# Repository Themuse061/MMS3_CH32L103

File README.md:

Schematic should be good, but I haven't done routing yet

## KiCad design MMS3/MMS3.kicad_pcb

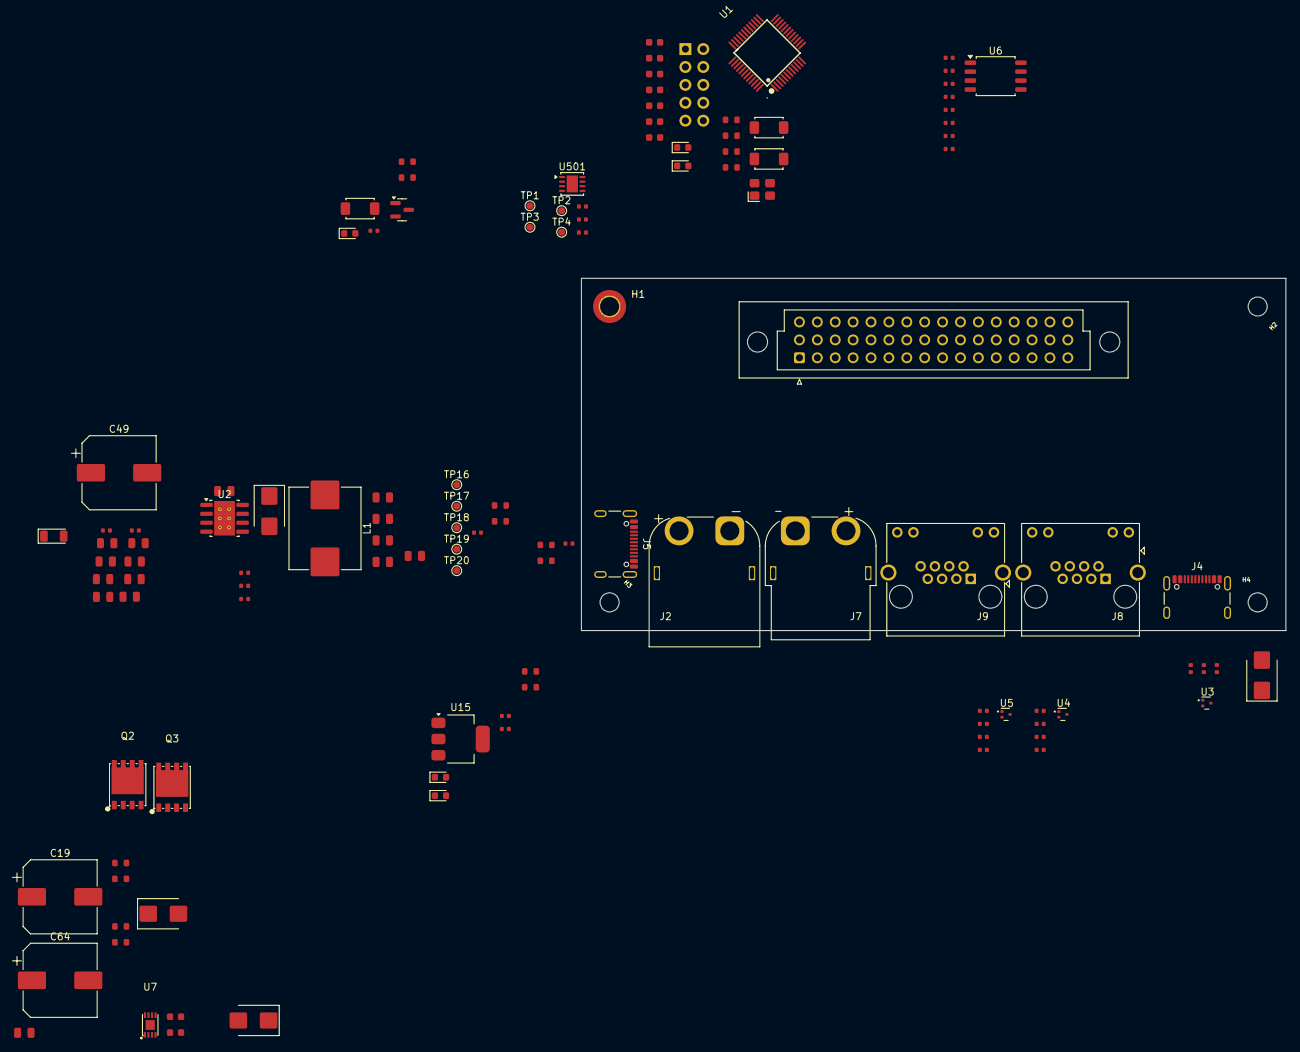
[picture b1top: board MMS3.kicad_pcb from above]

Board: 4 copper layers, 100.0 x 50.0 mm, 123 parts (1 on the bottom side), 77 nets, no tracks yet.

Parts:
C1, C2, C14: 10nF; C_0402
C3, C5: 12pF; C_0603
C4, C6, C15, C20, C27, C69, C74: 100nF; C_0402
C9, C10, C11, C12, C13, C16: 100nF; C_0603
C17: 1uF; C_0603
C18, C46, C47, C48, C50, C51: 22uF; C_0805
C19, C49, C64: 100uF; CP_Elec_10x10
C35, C36, C37, C38, C39, C40: 10uF; C_0805
C41, C42: 220nF; C_0805
C43: 47pF; C_0402
C44: 4.7nF; C_0402
C45: 100nF; C_0805
D1, D4, D6, D8, D9: Red; D_0603
D2: SMF58CA; D_SOD-123FL
D3, D5, D7, D10: SS510B; D_SMB
H1: M2.5 Mount; MountingHole_2.7mm_M2.5_DIN965_Pad_TopOnly
H2, H3, H4: M2.5 mount; MountingHole_2.7mm_M2.5
J1: 86093488324755V1LF; DIN41612_C2_3x16_Female_Vertical_THT
J2: AMASS XT60; AMASS_XT60PW-M_1x02_P7.20mm_Horizontal
J3: WCH Link; PinSocket_2x05_P2.54mm_Vertical
J4: USB_C_Receptacle_USB2.0_16P; USB_C_Receptacle_GCT_USB4105-xx-A_16P_TopMnt_Horizontal
J5: USB_PD; USB_C_Receptacle_GCT_USB4105-xx-A_16P_TopMnt_Horizontal
J7: AMASS XT60; AMASS_XT60PW-F_1x02_P7.20mm_Horizontal
J8, J9: RJ45_LED_Shielded; RJ45_Amphenol_RJHSE538X
L1: YSPI1050-100M; L_Sunlord_MWSA1005S
Q1: MMBT5401 200-300; Q_SOT-23
Q2, Q3: DOINGTER DON50N10-TL; PDFN-8_L5.8-W5.0-P1.27-LS6.1-BL
R1, R2, R3, R4: 220Ω; R_0402
R5, R6, R14: 33kΩ; R_0402
R7, R23, R24, R25, R26, R28, R29, R30, R501: 10kΩ; R_0402
R8: 1.5kΩ; R_0603
R9, R12, R13, R18: 1kΩ; R_0603
R10, R11: 10kΩ; R_0603
R15: 39kΩ; R_0603
R16: 12kΩ; R_0603
R17: 4.7kΩ; R_0603
R19: 47kΩ; R_0603
R20: 18kΩ; R_0603
R21, R22: 5.1kΩ; R_0603
R33, R34: 24.9kΩ; R_0402
R36: 43kΩ; R_0603
R37: 8.2kΩ; R_0402
R38: 12kΩ; R_0402
R39: 240kΩ; R_0603
S1, S2, S3: Tactile Button, 160gf; SW_TS-1088-AR02016
TP1, TP2, TP3, TP4, TP16, TP17, TP18, TP19, TP20: TestPoint; TestPoint_Pad_D1.0mm
U1: CH32L103C8T6_C22398291; LQFP-48_L7.0-W7.0-P0.50-LS9.0-BL
U2: TPS54560BDDA; Texas_R-PDSO-G8_EP2.95x4.9mm_Mask2.4x3.1mm_ThermalVias
U3, U4, U5: TPD2EUSB30DRTR-TP; SOT-723
U6: AT24C256C; SOIC-8_5.3x5.3mm_P1.27mm
U7: MX74502D23_C41433189; UDFN-8L_L2.0-W3.0-P0.50-BL-EP
U15: AMS1117-3.3; SOT-223-3_TabPin2
U501: TJA1044GTK_3Z; HVSON-8-1EP_3x3mm_P0.65mm_EP1.6x2.4mm
X1: X322525MOB4SI; OSC-SMD_4P-L3.2-W2.5-BL

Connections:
+3V3: C4.1, C9.1, C10.1, C11.1, C12.1, C13.1, C27.1, C69.1, D9.2, Q1.2 (E), R2.2, R3.2, R11.2, R28.1, R29.1, R30.1, S1.1 (A), S2.2 (B), U1.1 (VBAT), U1.9 (VDDA), U1.24 (VDD), U1.36 (VDD), U1.48 (VDD), U6.8 (VCC), U15.2 (VO), U501.5 (VIO)
+5V: C6.2, C19.1, C64.1, C74.1, D5.1, D7.1, D8.2, D10.1, J1.c2, J1.c3, J3.10, U15.3 (VI), U501.3 (VCC)
+12V stby: J1.c15, J8.6, J9.6
/CAN_TR2/CAN.+: J8.5, J9.5, U501.7 (CANH)
/CAN_TR2/CAN.-: J8.4, J9.4, U501.6 (CANL)
/CAN_TR2/CAN.RX: TP1.1 (1_1), TP4.1 (1_1), U1.45 (PB8), U501.4 (RXD)
/CAN_TR2/CAN.TX: TP2.1 (1_1), TP3.1 (1_1), U1.46 (PB9), U501.1 (TXD)
/CH32L103_Wrapper/CH32L103/BOOT0: R10.1, S2.1 (A), U1.44 (BOOT0)
/CH32L103_Wrapper/CH32L103/I2C1.SCL: J5.A5 (CC1), R22.1, U1.42 (PB6/CC1)
/CH32L103_Wrapper/CH32L103/I2C1.SDA: J5.B5 (CC2), R21.1, U1.43 (PB7/CC2)
/CH32L103_Wrapper/CH32L103/OSC_IN: C3.2, U1.5 (OSC_IN/PD0), X1.1 (OSC)
/CH32L103_Wrapper/CH32L103/OSC_Out: C5.2, U1.6 (OSC_OUT/PD1), X1.3 (OSC)
/CH32L103_Wrapper/CH32L103/PA13 (SWDIO): J3.4, U1.34 (PA13/SWDIO)
/CH32L103_Wrapper/CH32L103/PA14 (SWCLK): J3.2, U1.37 (PA14/SWCLK)
/CH32L103_Wrapper/CH32L103/UART1.RX: J3.3, R7.1, S1.2 (B), U1.31 (PA10)
/CH32L103_Wrapper/CH32L103/UART1.TX: D1.2, J3.1, U1.30 (PA9)
/CH32L103_Wrapper/CH32L103/~RST: J3.9, R11.1, S3.1 (A), U1.7 (NRST)
/CH32L103_Wrapper/Chainbus_addr0: J1.b3, U1.12 (PA2/ADC2/OPAO2)
/CH32L103_Wrapper/Chainbus_addr1: J1.b4, U1.13 (PA3/ADC3/OPAO0)
/CH32L103_Wrapper/Chainbus_addr2: J1.b5, U1.14 (PA4/ADC4/OPAO3)
/CH32L103_Wrapper/Chainbus_addr3: D4.1, J1.b1, U1.10 (PA0/WKUP/ADC0/OPAP4)
/CH32L103_Wrapper/Chainbus_addr4: J1.b2, U1.11 (PA1/ADC1/OPAN4)
/CH32L103_Wrapper/Chainbus_addr5: J1.b6, U1.15 (PA5/ADC5/OPAN3)
/CH32L103_Wrapper/Chainbus_addr6: J1.b7, U1.16 (PA6/ADC6/OPAP5/OPAN1)
/CH32L103_Wrapper/Chainbus_addr7: J1.b8, U1.17 (PA7/ADC7/OPAP3/OPAN5)
/CH32L103_Wrapper/I2C2.SCL: J1.b10, U1.22 (PB11/OPAN0), U6.6 (SCL)
/CH32L103_Wrapper/I2C2.SDA: J1.b9, U1.21 (PB10/OPAN2/OPAN6), U6.5 (SDA)
/CH32L103_Wrapper/PC13: D6.1, R8.1, U1.2 (PC13/TAMPER/RTC)
/CH32L103_Wrapper/SPI2.CS: J1.b11, U1.25 (PB12)
/CH32L103_Wrapper/SPI2.MISO: J1.b14, U1.28 (PB15/OPAP0)
/CH32L103_Wrapper/SPI2.MOSI: J1.b13, U1.27 (PB14/OPAP2)
/CH32L103_Wrapper/SPI2.SCK: J1.b12, U1.26 (PB13)
/CH32L103_Wrapper/UART4.RX: J1.b15, U1.19 (PB1/ADC9/OPAO1)
/CH32L103_Wrapper/UART4.TX: J1.b16, U1.18 (PB0/ADC8/OPAP1/OPAO4)
/CH32L103_Wrapper/USB1.D+: J4.A6 (D+), J4.B6 (D+), U1.33 (PA12/UDP), U3.1
/CH32L103_Wrapper/USB1.D-: J4.A7 (D-), J4.B7 (D-), U1.32 (PA11/UDM), U3.2
/I2C_Flash/A0: R23.1, R28.2, U6.1 (A0)
/I2C_Flash/A1: R24.1, R29.2, U6.2 (A1)
/I2C_Flash/A2: R25.1, R30.2, U6.3 (A2)
/MMS_CONNECTOR_DOWNSTREAM/CAN1.+: J8.2, J9.2
/MMS_CONNECTOR_DOWNSTREAM/CAN1.-: J8.1, J9.1
/MMS_CONNECTOR_DOWNSTREAM/USB_MMS_CONN.D+: J8.8, J9.8, U4.2, U5.2
/MMS_CONNECTOR_DOWNSTREAM/USB_MMS_CONN.D-: J8.7, J9.7, U4.1, U5.1
/PSU/Buck Converter/5V out: C46.1, C47.1, C48.1, C50.1, C51.1, D7.2, L1.2, R36.1, TP19.1 (1_1)
/PSU/Buck Converter/Cap_protec: C35.2, C36.1, C37.2, C38.1, C39.2, C40.1, C41.2, C42.1, R33.2, R34.1
/PSU/EN: R15.2, R16.1
/PSU/NMos1/D: C18.1, D10.2, Q3.5 (D), Q3.6 (D), Q3.7 (D), Q3.8 (D), Q3.9 (D)
/PSU/NMos/G: Q2.4 (G), Q3.4 (G), U7.2 (GATE)
/PSU/NMos/S: Q2.1 (S), Q2.2 (S), Q2.3 (S), Q3.1 (S), Q3.2 (S), Q3.3 (S), U7.3 (SRC)
/RXD2_LED: Q1.3 (C), R4.2
/TXD2_LED: R1.2, U1.20 (PB2/BOOT1)
/USB_Data/VBUS: C15.1, D5.2, J4.A4 (VBUS), J4.A9 (VBUS), J4.B4 (VBUS), J4.B9 (VBUS)
BRD_VIN: C16.1, C17.1, C20.1, C35.1, C37.1, C39.1, C41.1, C49.1, D2.1, J1.c5, J1.c6, J1.c7, J1.c8, J2.2, J5.A4 (VBUS), J5.A9 (VBUS), J5.B4 (VBUS), J5.B9 (VBUS), J7.2, Q2.5 (D), Q2.6 (D), Q2.7 (D), Q2.8 (D), Q2.9 (D), R15.1, R19.1, R33.1, TP16.1 (1_1), U2.2 (VIN), U2.3 (EN), U7.1 (VS), U7.5 (EN/UVLO)
GND: C1.2, C2.2, C3.1, C4.2, C5.1, C6.1, C9.2, C10.2, C11.2, C12.2, C13.2, C14.2, C15.2, C16.2, C18.2, C19.2, C20.2, C27.2, C36.2, C38.2, C40.2, C42.2, C43.2, C44.2, C46.2, C47.2, C48.2, C49.2, C50.2, C51.2, C64.2, C69.2, C74.2, D2.2, D3.2, H1.1 (1_1), J1.c1, J1.c4, J1.c9, J1.c10, J1.c11, J1.c12, J1.c16, J2.1, J3.6, J4.A1 (GND), J4.A12 (GND), J4.B1 (GND), J4.B12 (GND), J5.A1 (GND), J5.A12 (GND), J5.B1 (GND), J5.B12 (GND), J7.1, J8.3, J8.9, J8.11, J9.3, J9.9, J9.11, R5.2, R6.2, R7.2, R9.2, R10.2, R12.2, R13.2, R14.2, R16.2, R17.2, R18.2, R20.2, R21.2, R22.2, R23.2, R24.2, R25.2, R26.2, R34.2, R37.2, R39.2, R501.2, S3.2 (B), U1.8 (VSSA), U1.23 (VSS), U1.35 (VSS), U1.47 (VSS), U2.7 (GND), U2.9 (GND), U3.3, U4.3, U5.3, U6.4 (GND), U7.4 (GND), U15.1 (GND), U501.2 (GND), U501.9 (EP), X1.2 (GND), X1.4 (GND)
unnamed: C1.1, J8.SH, R5.1
unnamed: C2.1, J9.SH, R6.1
unnamed: C44.1, R38.2
unnamed: D1.1, R9.1
unnamed: D4.2, R12.1
unnamed: D6.2, R13.1
unnamed: D8.1, R17.1
unnamed: D9.1, R18.1
unnamed: C14.1, J4.SH (SHIELD), R14.1
unnamed: J8.10, R1.1
unnamed: J8.12, R3.1
unnamed: J9.10, R2.1
unnamed: J9.12, R4.1
unnamed: Q1.1 (B), R8.2
unnamed: C45.2, U2.1 (BOOT)
unnamed: C43.1, R38.1, TP17.1 (1_1), U2.6 (COMP)
unnamed: R36.2, R37.1, TP18.1 (1_1), U2.5 (FB)
unnamed: R39.1, TP20.1 (1_1), U2.4 (RT/CLK)
unnamed: C45.1, D3.1, L1.1, U2.8 (SW)
unnamed: R26.1, U6.7 (WP)
unnamed: R19.2, R20.1, U7.7 (OV)
unnamed: C17.2, U7.8 (VCAP)
unnamed: R501.1, U501.8 (STB)

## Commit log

2026-05-13 changed most of stuff to ch32L103
2026-05-16 backup commit
2026-05-16 kinda finished schematic
2026-05-21 updated schematic, removed annotation
2026-05-21 initial PCB update
2026-05-22 re-added onboard programmer
